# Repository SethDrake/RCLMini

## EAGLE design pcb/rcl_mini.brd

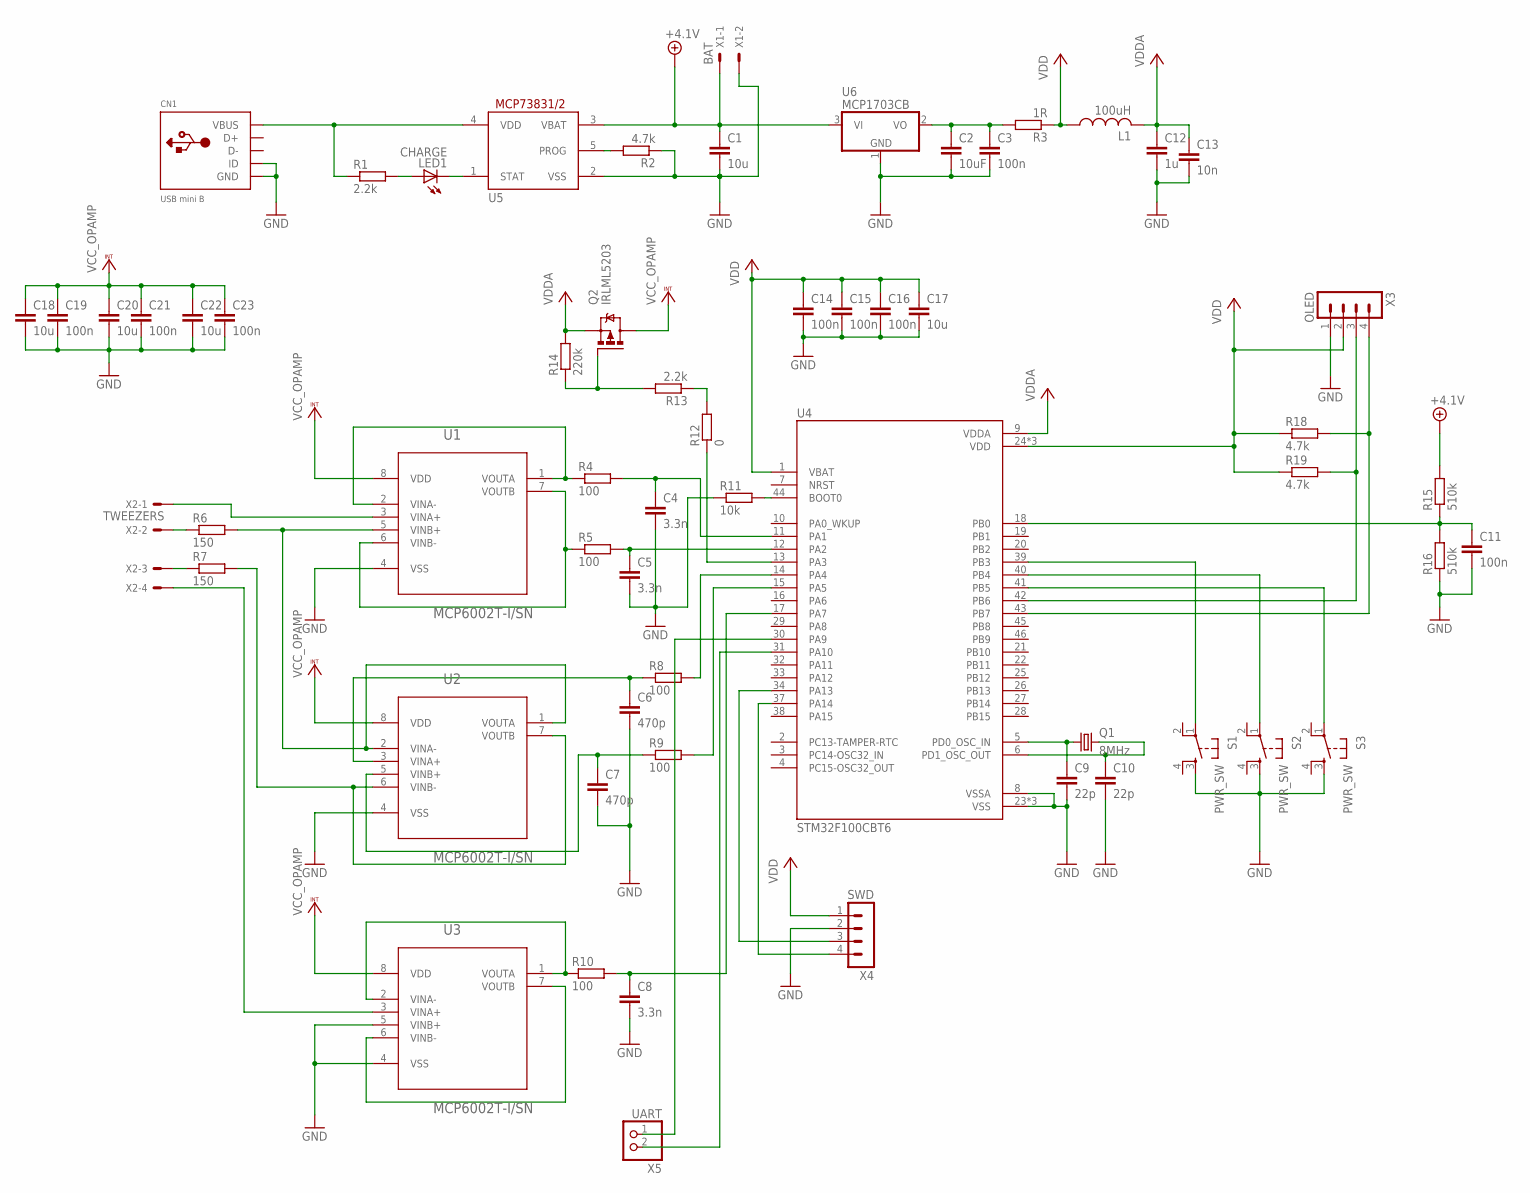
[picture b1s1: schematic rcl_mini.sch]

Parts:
C1, C17, C18, C20, C22: 10u; C0805
C2: 10uF; C0805
C3, C11, C14, C15, C16, C19, C21, C23: 100n; C0805
C4, C5, C8: 3.3n; C0805
C6, C7: 470p; C0805
C9, C10: 22p; C0805
C12: 1u; C0805
C13: 10n; C0805
CN1: USB mini B; USB-MINIB
L1: 100uH; L3216C
LED1: CHARGE; CHIPLED_1206
Q1: 8MHz; HC49UP
Q2: IRLML5203; MICRO3
R1, R13: 2.2k; M0805
R2, R18, R19: 4.7k; M0805
R3: 1R; M0805
R4, R5, R8, R9, R10: 100; M0805
R6, R7: 150; M0805
R11: 10k; M0805
R12: 0; R1206
R14: 220k; M0805
R15, R16: 510k; M0805
S1, S2, S3: PWR_SW; DTS-6
U1, U2, U3: MCP6002T-I/SN; SOIC127P600X175-8N
U4: STM32F100CBT6; QFP50P900X900X160-48N
U5: MCP73831/OT; SOT23-5L
U6: MCP1703CB; SOT23
UART: X5; 1X02
X1: BAT; 22-23-2021
X2: TWEEZERS; 22-23-2041
X3: OLED; MA04-1
X4: SWD; MA04-1

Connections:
GND: C1.2, C2.2, C3.2, C4.2, C5.2, C6.2, C7.2, C8.2, C9.2, C10.2, C11.2, C12.2, C13.2, C14.2, C15.2, C16.2, C17.2, C18.2, C19.2, C20.2, C21.2, C22.2, C23.2, CN1.GND, CN1.ID, R2.1, R11.1, R16.1, S1.3, S2.3, S3.3, U1.4 (VSS), U2.4 (VSS), U3.4 (VSS), U3.5 (VINB+), U4.8 (VSSA), U4.23 (VSS), U4.35 (VSS), U4.47 (VSS), U5.2 (VSS), U6.1 (GND), X1.2, X3.1, X4.2
HCUR: R7.1, X2.3
HCUR2: R7.2, U2.6 (VINB-), U2.7 (VOUTB)
HPOT: U3.3 (VINA+), X2.4
LCUR: R6.1, X2.2
LCUR2: R6.2, U1.5 (VINB+), U2.1 (VOUTA), U2.2 (VINA-)
unnamed: R12.2, R13.1
unnamed: LED1.A, R1.2
unnamed: LED1.C, U5.1 (STAT)
unnamed: R2.2, U5.5 (PROG)
unnamed: C2.1, C3.1, R3.2, U6.2 (VO)
unnamed: R4.1, U1.1 (VOUTA), U1.2 (VINA-)
unnamed: U1.3 (VINA+), X2.1
unnamed: R5.1, U1.6 (VINB-), U1.7 (VOUTB)
unnamed: C6.1, R8.1, U2.3 (VINA+)
unnamed: R11.2, U4.44 (BOOT0)
unnamed: Q2.1 (G), R13.2, R14.1
unnamed: C7.1, R9.1, U2.5 (VINB+)
unnamed: R10.1, U3.1 (VOUTA), U3.2 (VINA-)
unnamed: C11.1, R15.1, R16.2, U4.18 (PB0)
unnamed: U3.6 (VINB-), U3.7 (VOUTB)
unnamed: C9.1, Q1.1, U4.5 (PD0_OSC_IN)
unnamed: C10.1, Q1.2, U4.6 (PD1_OSC_OUT)
OLED_I2C_SCK: R19.2, U4.42 (PB6), X3.3
OLED_I2C_SDA: R18.2, U4.43 (PB7), X3.4
PA1: C4.1, R4.2, U4.11 (PA1)
PA2: C5.1, R5.2, U4.12 (PA2)
PA3: R12.1, U4.13 (PA3)
PA4: R8.2, U4.14 (PA4)
PA5: R9.2, U4.15 (PA5)
PA7: C8.1, R10.2, U4.17 (PA7)
SW1: S1.1, U4.39 (PB3)
SW2: S2.1, U4.40 (PB4)
SW3: S3.1, U4.41 (PB5)
SWCLK: U4.37 (PA14), X4.4
SWDIO: U4.34 (PA13), X4.3
UART_RX: U4.31 (PA10), UART.2
UART_TX: U4.30 (PA9), UART.1
USB+: CN1.VBUS, R1.1, U5.4 (VDD)
VBAT+: C1.1, R15.2, U5.3 (VBAT), U6.3 (VI), X1.1
VCC_OPAMP: C18.1, C19.1, C20.1, C21.1, C22.1, C23.1, Q2.3 (D), U1.8 (VDD), U2.8 (VDD), U3.8 (VDD)
VDD: C14.1, C15.1, C16.1, C17.1, L1.1, R3.1, R18.1, R19.1, U4.1 (VBAT), U4.24 (VDD), U4.36 (VDD), U4.48 (VDD), X3.2, X4.1
VDDA: C12.1, C13.1, L1.2, Q2.2 (S), R14.2, U4.9 (VDDA)

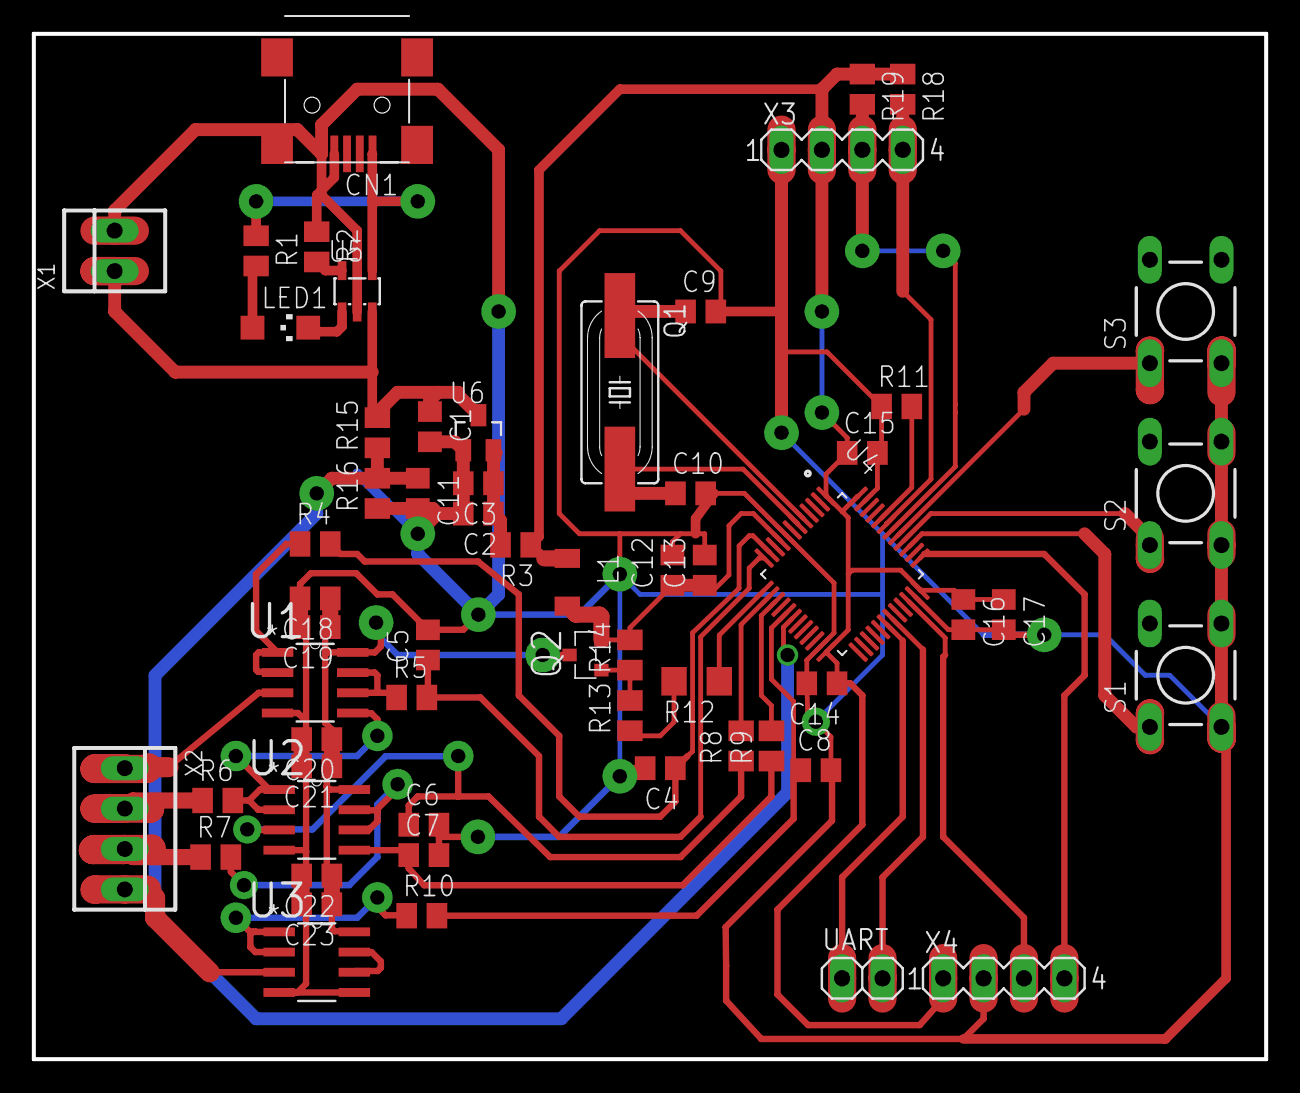
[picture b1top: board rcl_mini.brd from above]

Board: 2 copper layers, 77.5 x 64.4 mm, 60 parts (0 on the bottom side), 43 nets.

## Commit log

2019-11-09 pcb v1.0
2019-11-14 pcb v1.0 completed
2019-11-16 adopted firmware from Nikitos https://radiokot.ru/circuit/digital/measure/108/ https://drive.google.com/drive/folders/0B6ejWgMiaZIvfm1nM1FLalNya0xEcTRqZkZqQ01XcEJ2UTZBb014Ym9majBQMXFZc2xYTW8
2019-11-16 fw improvements
2019-12-12 mcp6002 package was changed from msop to soic
2019-12-12 pcb design improvements
2020-02-17 added SH1106 support (ssd1306 commented)
